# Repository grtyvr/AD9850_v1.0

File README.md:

# AD9850_v1.0
Larger version of the board for the SigGen project: 328p based AD9850 function generator.

It is based on the project:

http://www.vwlowen.co.uk/arduino/AD9850-waveform-generator/AD9850-waveform-generator.htm

Which in turn is based on AD9851 code from Andrew Smallbone - modified for AD9850
   http://www.rocketnumbernine.com/2011/10/25/programming-the-ad9851-dds-synthesizer

I have created the KiCad files for a board for this project.  This version takes out the 100K current limiting resistor for the display led (on is on the board already).  And it is powered not by a power jack but by pin header from a seperate power supply in the same case.

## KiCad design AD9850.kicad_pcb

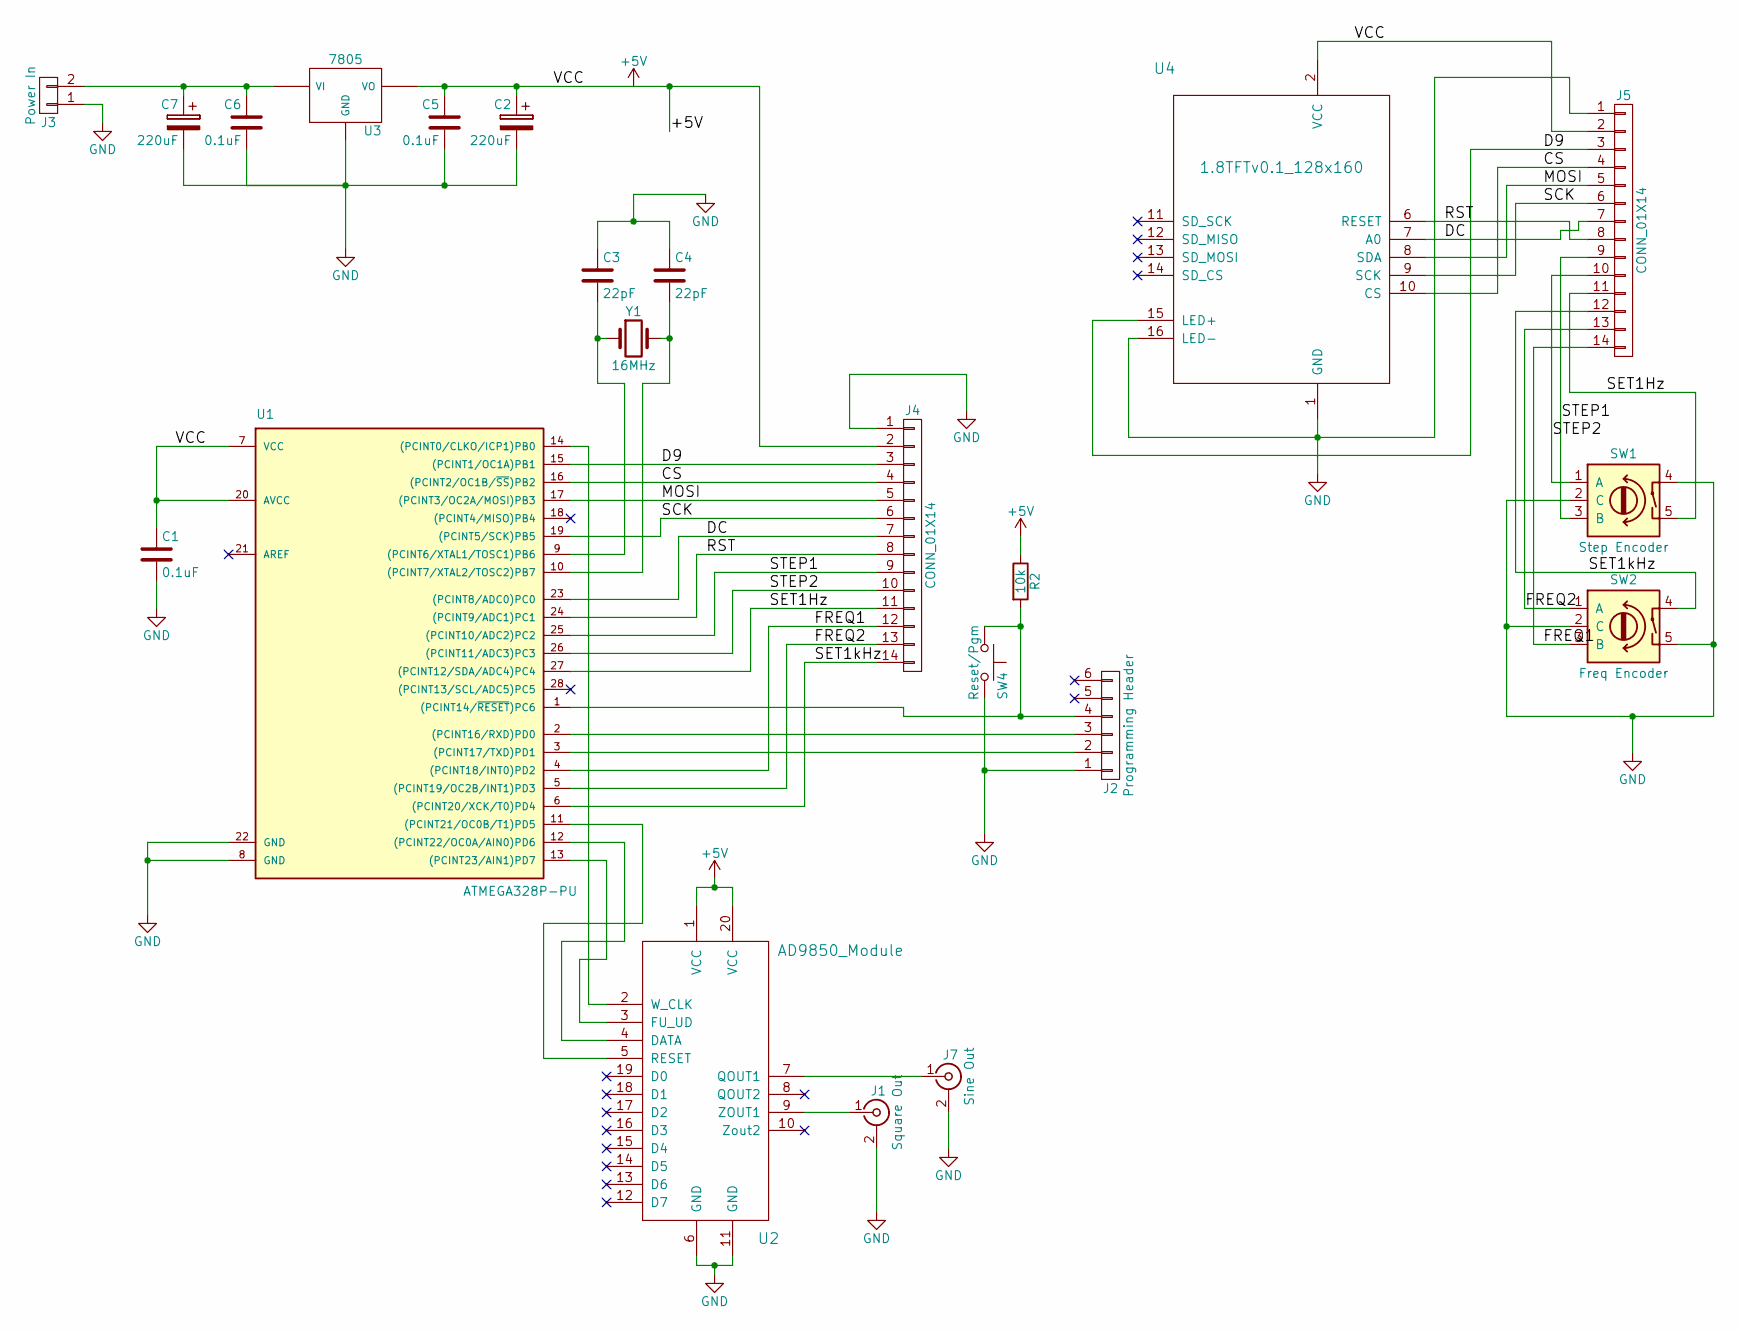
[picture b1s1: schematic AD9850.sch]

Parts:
C1, C5: 0.1uF; C_Disc_D3.0mm_W1.6mm_P2.50mm
C2, C7: 220uF; CP_Radial_D8.0mm_P3.50mm
C3, C4: 22pF; C_Disc_D3.0mm_W1.6mm_P2.50mm
C6: 0.1uF; C_Disc_D3.0mm_W2.0mm_P2.50mm
J1: Square Out; BNC_Socket_TYCO-AMP
J2: Programming Header; Pin_Header_Straight_1x06_Pitch2.54mm
J3: Power In; GTK2400-V2
J4, J5: CONN_01X14; Pin_Header_Straight_1x14_Pitch2.54mm
J7: Sine Out; BNC_Socket_TYCO-AMP
R2: 10k; D3
SW1: Step Encoder; SF-ROTARY-ENCODER
SW2: Freq Encoder; SF-ROTARY-ENCODER
SW4: Reset/Pgm; SW_PUSH_6mm
U1: ATMEGA328P-PU; DIP-28_W7.62mm
U2: AD9850_Module; DS9850_Module
U3: 7805; TO-220
U4: 1.8TFTv0.1_128x160; 128x160-SPI_w_SD-CARD
Y1: 16MHz; Crystal_AT310_d3.0mm_l10.0mm_Horizontal

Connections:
+5V: C1.1, C2.1, C5.1, J4.2, J5.2, R2.1, U1.7 (VCC), U1.20 (AVCC), U2.1 (VCC), U2.20 (VCC), U3.VO, U4.2 (VCC)
/CS: J4.4, J5.4, U1.16 ((PCINT2/OC1B/~SS~)PB2), U4.10 (CS)
/D9: J4.3, J5.3, U1.15 ((PCINT1/OC1A)PB1), U4.15 (LED+)
/DC: J4.7, J5.7, U1.23 ((PCINT8/ADC0)PC0), U4.7 (A0)
/FREQ1: J4.12, J5.14, SW2.3 (B), U1.4 ((PCINT18/INT0)PD2)
/FREQ2: J4.13, J5.13, SW2.1 (A), U1.5 ((PCINT19/OC2B/INT1)PD3)
/MOSI: J4.5, J5.5, U1.17 ((PCINT3/OC2A/MOSI)PB3), U4.8 (SDA)
/RST: J4.8, J5.8, U1.24 ((PCINT9/ADC1)PC1), U4.6 (RESET)
/SCK: J4.6, J5.6, U1.19 ((PCINT5/SCK)PB5), U4.9 (SCK)
/SET1Hz: J4.11, J5.11, SW1.5, U1.27 ((PCINT12/SDA/ADC4)PC4)
/SET1kHz: J4.14, J5.12, SW2.4, U1.6 ((PCINT20/XCK/T0)PD4)
/STEP1: J4.9, J5.9, SW1.3 (B), U1.25 ((PCINT10/ADC2)PC2)
/STEP2: J4.10, J5.10, SW1.1 (A), U1.26 ((PCINT11/ADC3)PC3)
GND: C1.2, C2.2, C3.1, C4.1, C5.2, C6.2, C7.2, J1.2 (Ext), J2.1, J3.1, J4.1, J5.1, J7.2 (Ext), SW1.2 (C), SW1.4, SW2.2 (C), SW2.5, SW4.2, U1.8 (GND), U1.22 (GND), U2.6 (GND), U2.11 (GND), U3.GND, U4.1 (GND), U4.16 (LED-)
unnamed: C3.2, U1.9 ((PCINT6/XTAL1/TOSC1)PB6), Y1.1
unnamed: C4.2, U1.10 ((PCINT7/XTAL2/TOSC2)PB7), Y1.2
unnamed: C6.1, C7.1, J3.2, U3.VI
unnamed: J1.1 (In), U2.9 (ZOUT1)
unnamed: J2.2, U1.3 ((PCINT17/TXD)PD1)
unnamed: J2.3, U1.2 ((PCINT16/RXD)PD0)
unnamed: J2.4, R2.2, SW4.1, U1.1 ((PCINT14/~RESET~)PC6)
unnamed: J7.1 (In), U2.7 (QOUT1)
unnamed: U1.11 ((PCINT21/OC0B/T1)PD5), U2.5 (RESET)
unnamed: U1.12 ((PCINT22/OC0A/AIN0)PD6), U2.4 (DATA)
unnamed: U1.13 ((PCINT23/AIN1)PD7), U2.3 (FU_UD)
unnamed: U1.14 ((PCINT0/CLKO/ICP1)PB0), U2.2 (W_CLK)

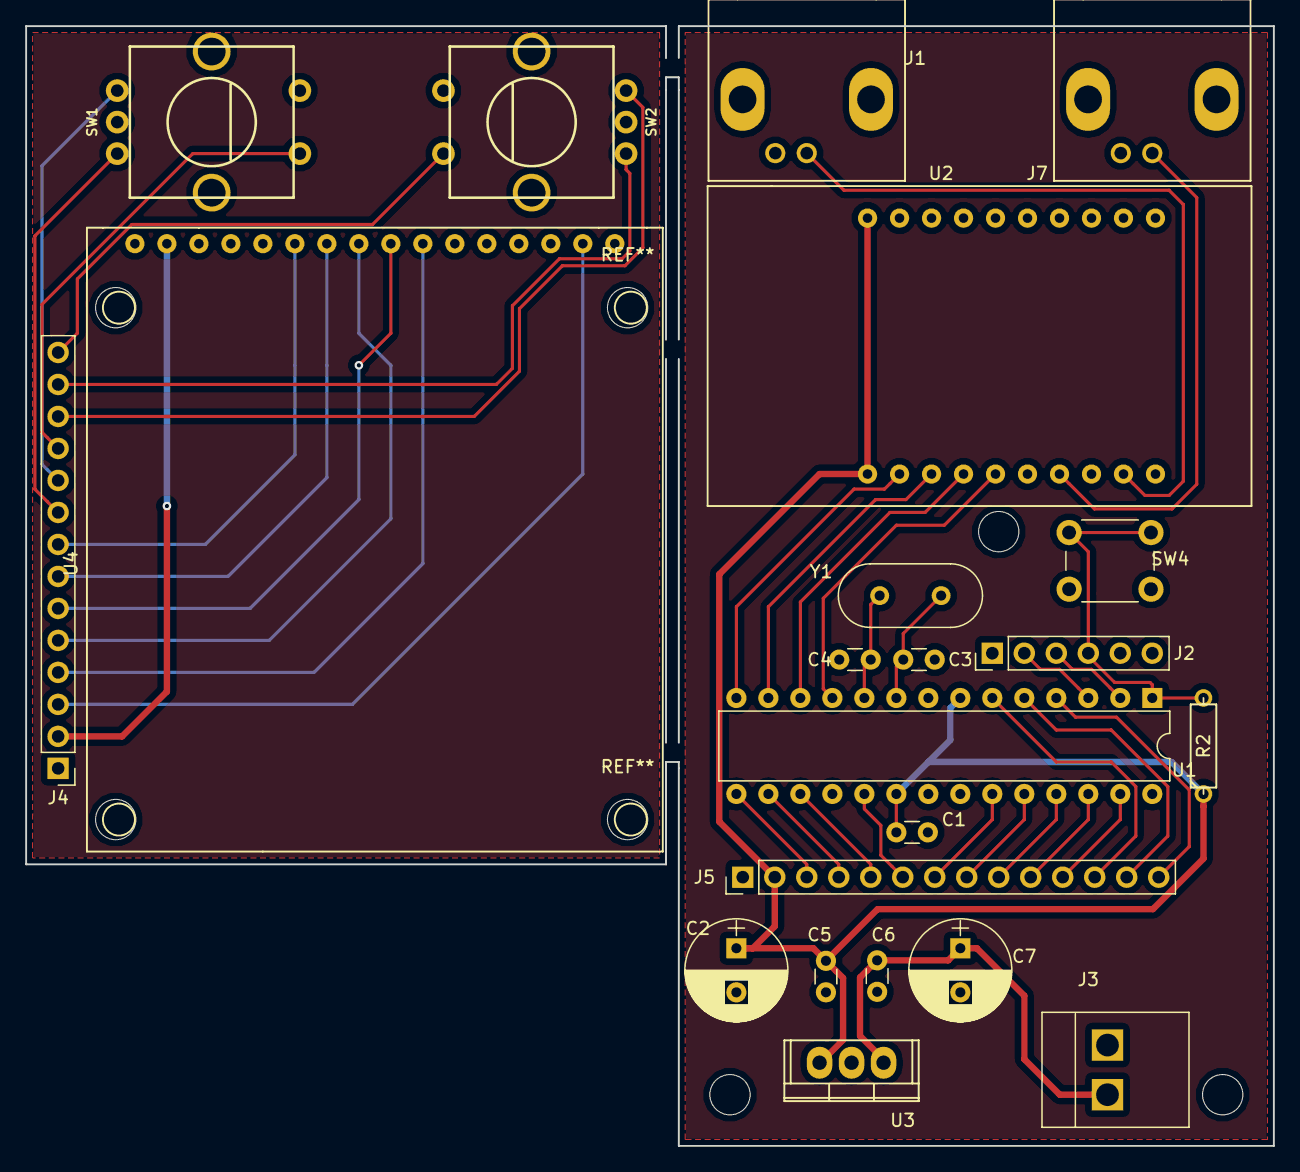
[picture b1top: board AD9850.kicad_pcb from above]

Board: 2 copper layers, 99.1 x 88.9 mm, 22 parts (0 on the bottom side), 26 nets.

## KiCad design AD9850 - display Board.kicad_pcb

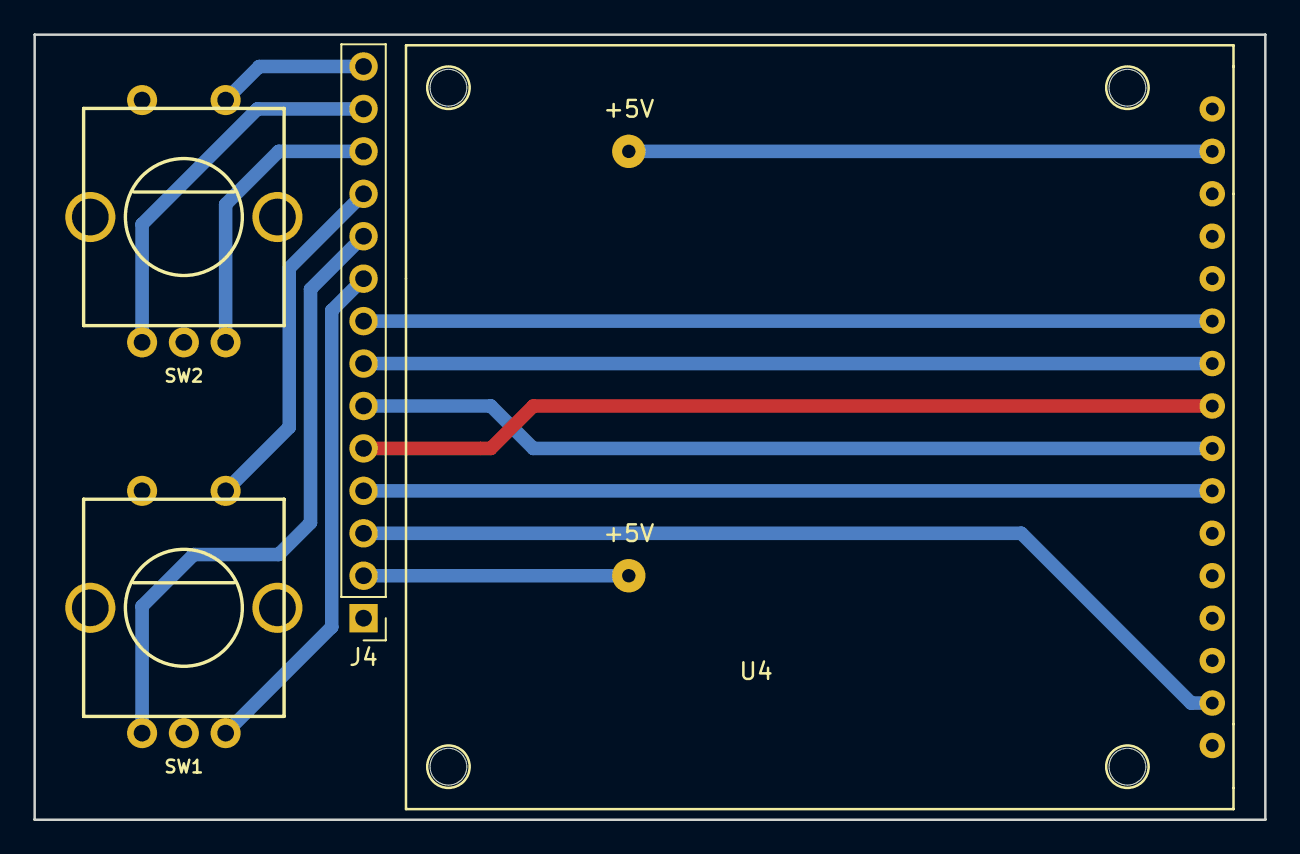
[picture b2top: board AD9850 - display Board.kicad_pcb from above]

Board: 2 copper layers, 73.7 x 47.0 mm, 6 parts (0 on the bottom side), 14 nets.

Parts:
+5V, +5V#2: JP2; SolderWirePad_single_0-8mmDrill
J4: CONN_01X14; Pin_Header_Straight_1x14_Pitch2.54mm
SW1, SW2: Rotary_Encoder_Switch; SF-ROTARY-ENCODER
U4: 1.8TFTv0.1_128x160; 128x160-SPI_w_SD-CARD

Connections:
+5V: +5V.1, +5V#2.1, J4.2, U4.2
/CS: J4.4, U4.10
/D9: J4.3, U4.15
/DC: J4.7, U4.7
/FREQ1: J4.12, SW2.3
/FREQ2: J4.13, SW2.1
/MOSI: J4.5, U4.8
/RST: J4.8, U4.6
/SCK: J4.6, U4.9
/SET1Hz: J4.11, SW1.5
/SET1kHz: J4.14, SW2.5
/STEP1: J4.9, SW1.3
/STEP2: J4.10, SW1.1
GND: J4.1, SW1.2, SW1.4, SW2.2, SW2.4, U4.1, U4.16

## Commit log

2018-02-23 added support files for the schematic and board
    Note that the display footprint has mounting holes in the wrong places. They need to be moved.
2018-02-23 Update README.md
    Added history and noted the changes from the other version.
2018-02-23 Create LICENSE
